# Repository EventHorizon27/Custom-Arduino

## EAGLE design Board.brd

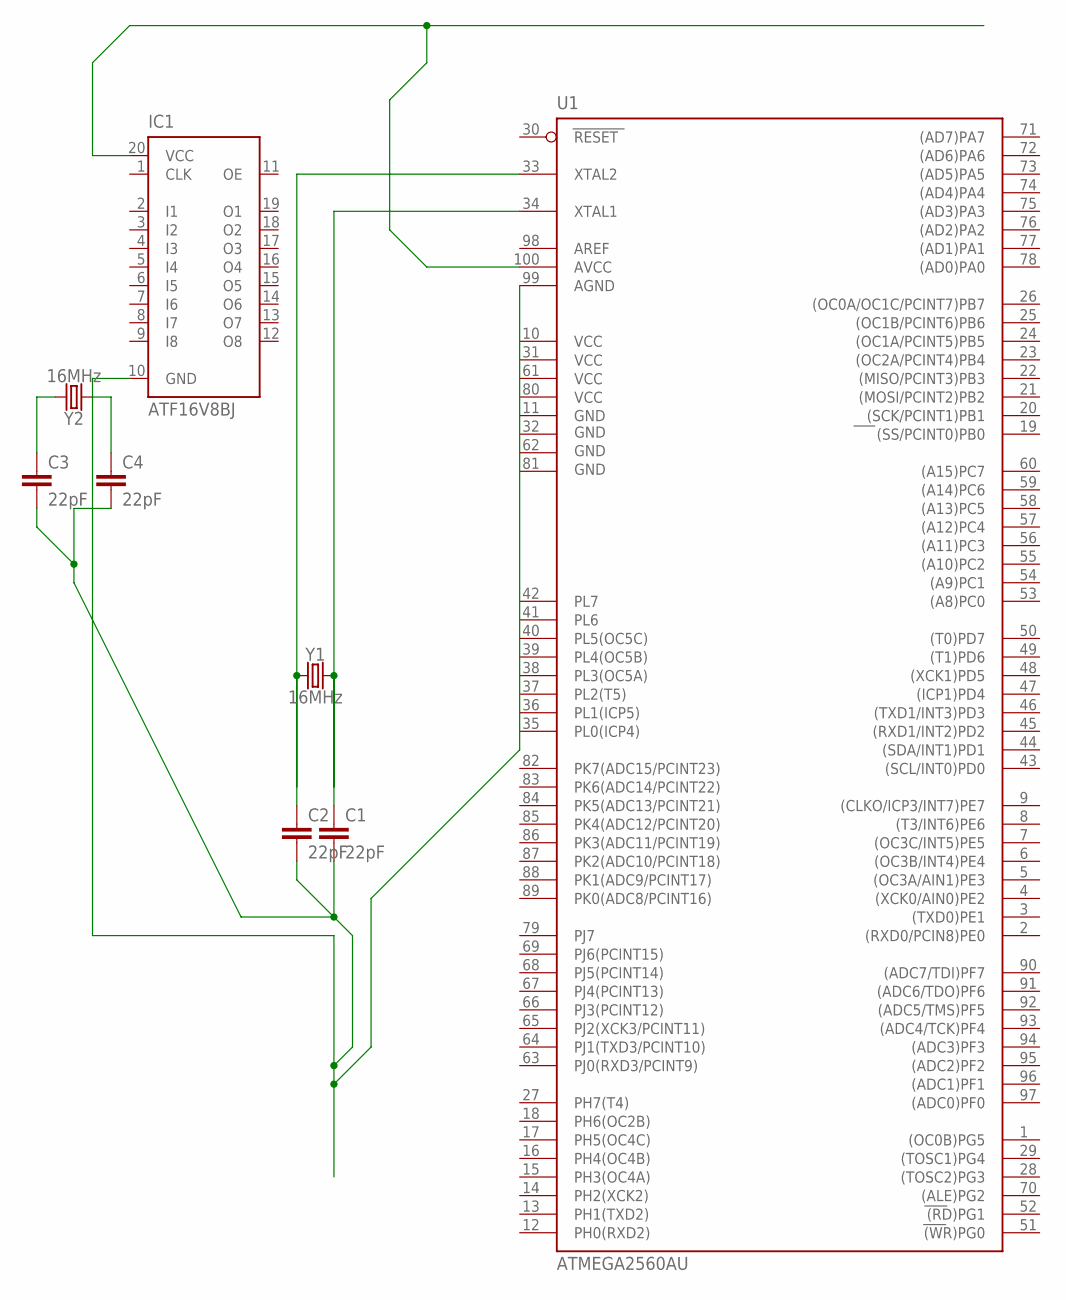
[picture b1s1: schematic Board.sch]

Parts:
C1, C2, C3, C4: 22pF; 0603
IC1: ATF16V8BJ; PLCC20
U1: ATMEGA2560AU; TQFP100
Y1, Y2: 16MHz; CRYSTAL-SMD-5X3.2-4PAD

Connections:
GND: U1.11 (GND)
GND1: U1.32 (GND1)
GND2: U1.62 (GND2)
GND3: U1.81 (GND3)
unnamed: IC1.20 (VCC), U1.100 (AVCC)
unnamed: C1.1, U1.34 (XTAL1), Y1.3 (2)
unnamed: C2.1, U1.33 (XTAL2), Y1.1
unnamed: C3.1, Y2.3 (2)
unnamed: C4.1, Y2.1
unnamed: C1.2, C2.2, C3.2, C4.2, IC1.10 (GND), U1.99 (AGND)
VCC: U1.10 (VCC)
VCC1: U1.31 (VCC1)
VCC2: U1.61 (VCC2)
VCC3: U1.80 (VCC3)

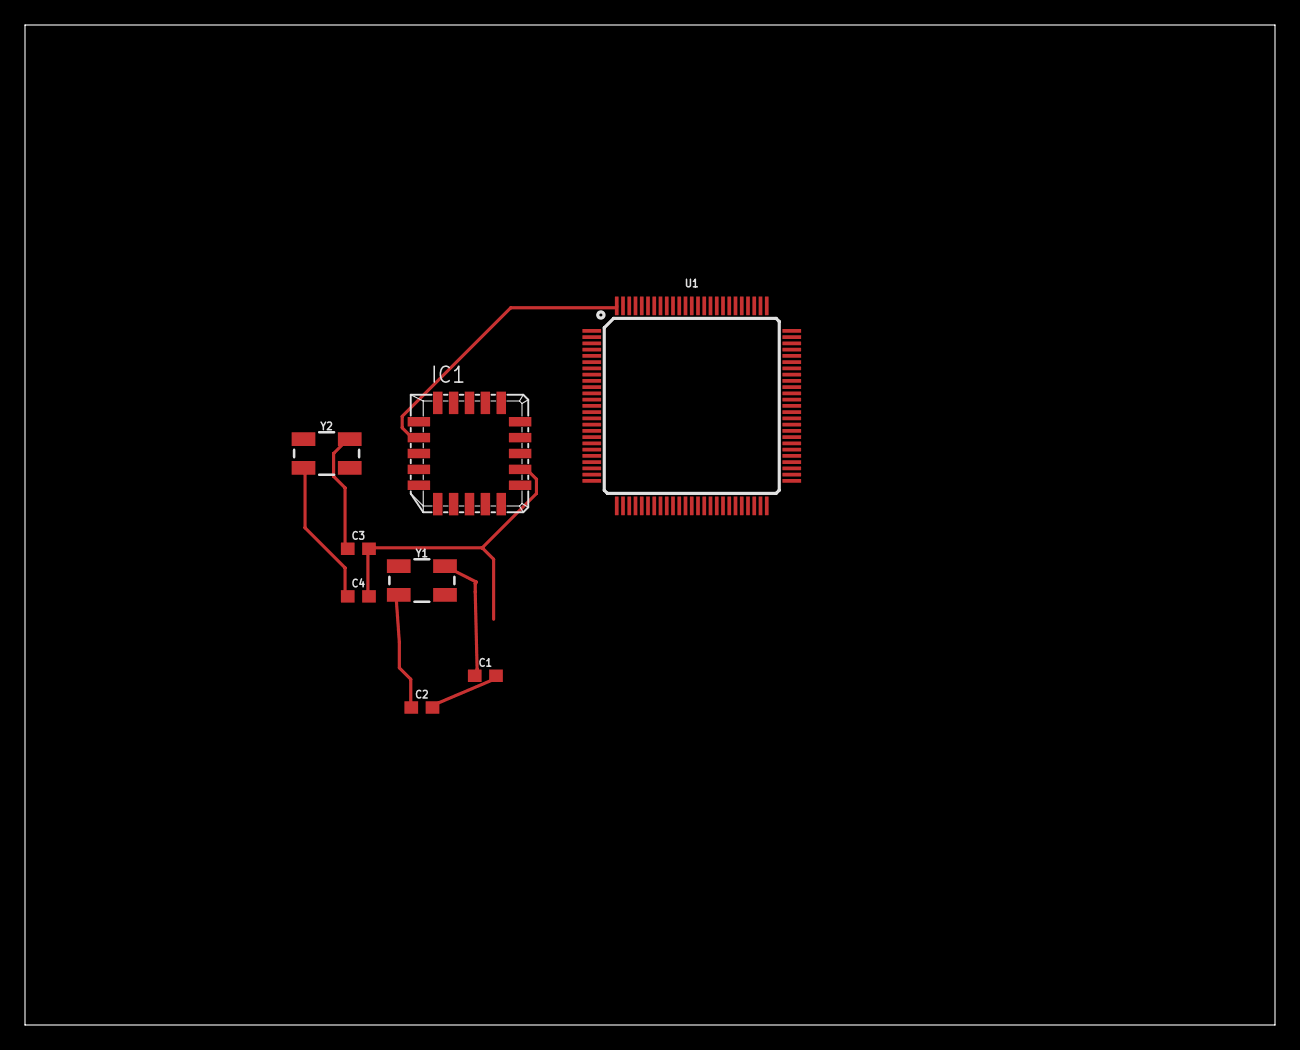
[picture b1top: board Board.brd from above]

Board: 2 copper layers, 100.0 x 80.0 mm, 8 parts (0 on the bottom side), 6 nets.

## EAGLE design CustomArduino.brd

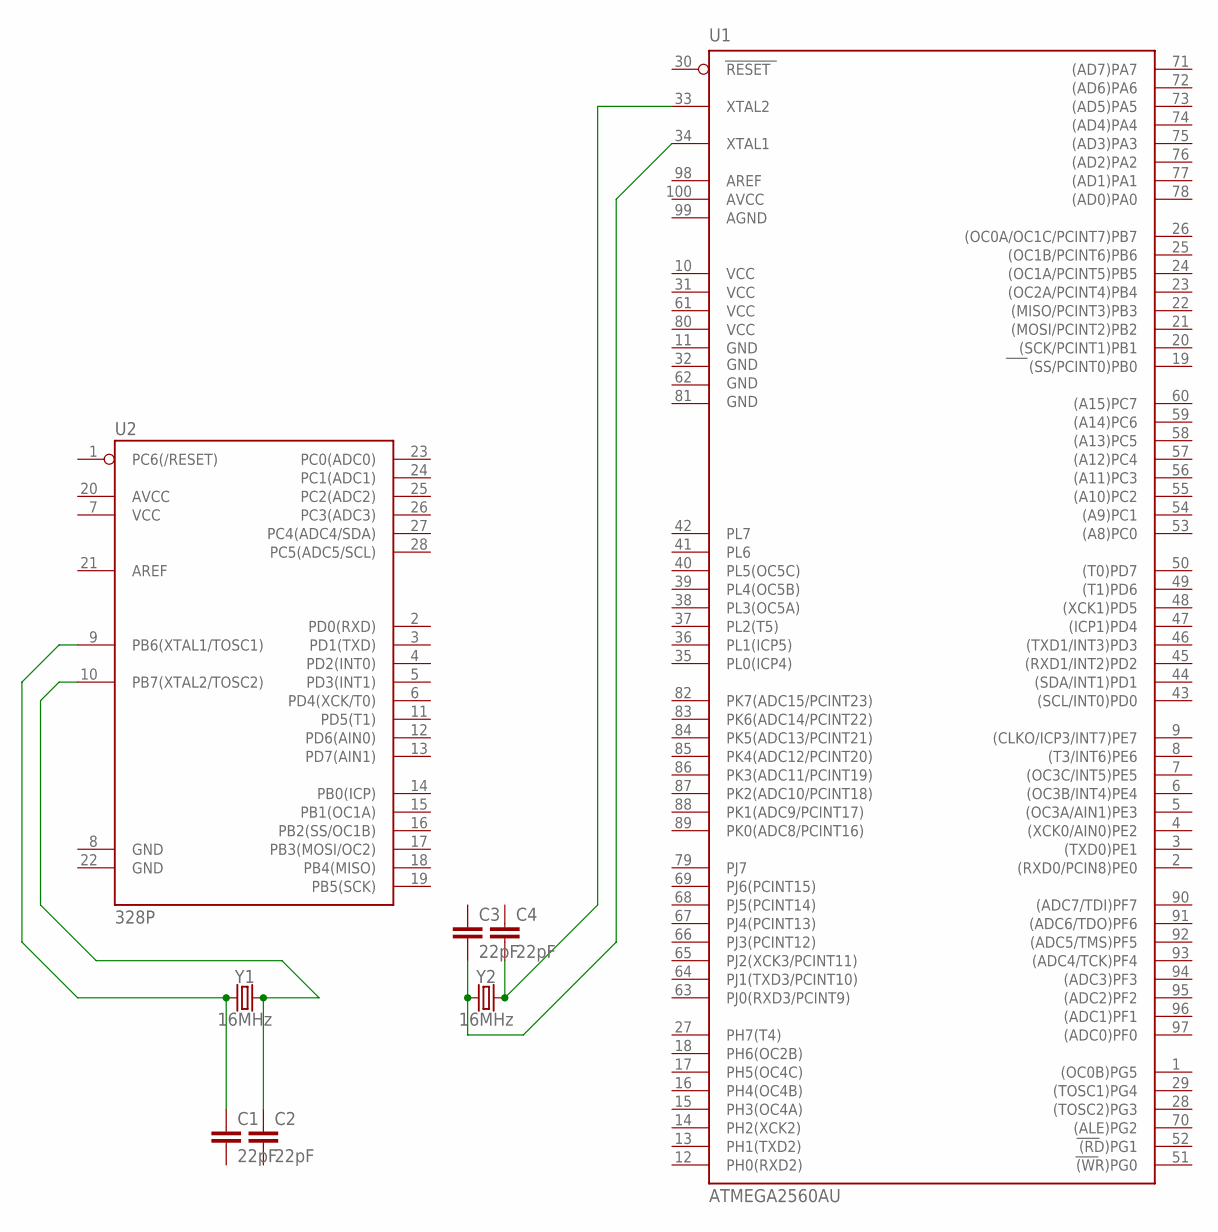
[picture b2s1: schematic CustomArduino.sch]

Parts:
C1, C2, C3, C4: 22pF; 0603
U1: ATMEGA2560AU; TQFP100
U2: 328P; DIP28
Y1, Y2: 16MHz; CRYSTAL-SMD-5X3.2-4PAD

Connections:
AGND: U1.99 (AGND)
AVCC: U1.100 (AVCC)
GND: U1.11 (GND)
GND1: U1.32 (GND1)
GND2: U1.62 (GND2)
GND3: U1.81 (GND3)
unnamed: C1.1, U2.9 (PB6(XTAL1/TOSC1)), Y1.1
unnamed: C4.2, U1.33 (XTAL2), Y2.3 (2)
unnamed: C3.2, U1.34 (XTAL1), Y2.1
unnamed: C2.1, U2.10 (PB7(XTAL2/TOSC2)), Y1.3 (2)
VCC: U1.10 (VCC)
VCC1: U1.31 (VCC1)
VCC2: U1.61 (VCC2)
VCC3: U1.80 (VCC3)

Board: 2 copper layers, 8 parts (0 on the bottom side), 4 nets, no tracks yet.

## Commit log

2017-03-10 added board.brd

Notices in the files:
parts and their libraries:
SparkFun-IC-Microcontroller: Licensing: Creative Commons ShareAlike 4.0 International - https://creativecommons.org/licenses/by-sa/4.0
